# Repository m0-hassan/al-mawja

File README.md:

# AL-MAWJA

KiCad project for a mixed-signal I/Q analog front-end board (iCE40 FPGA, FT2232H USB, AD7380 ADC).

Work in progress — schematic is done, board layout is still underway. Not finished yet.

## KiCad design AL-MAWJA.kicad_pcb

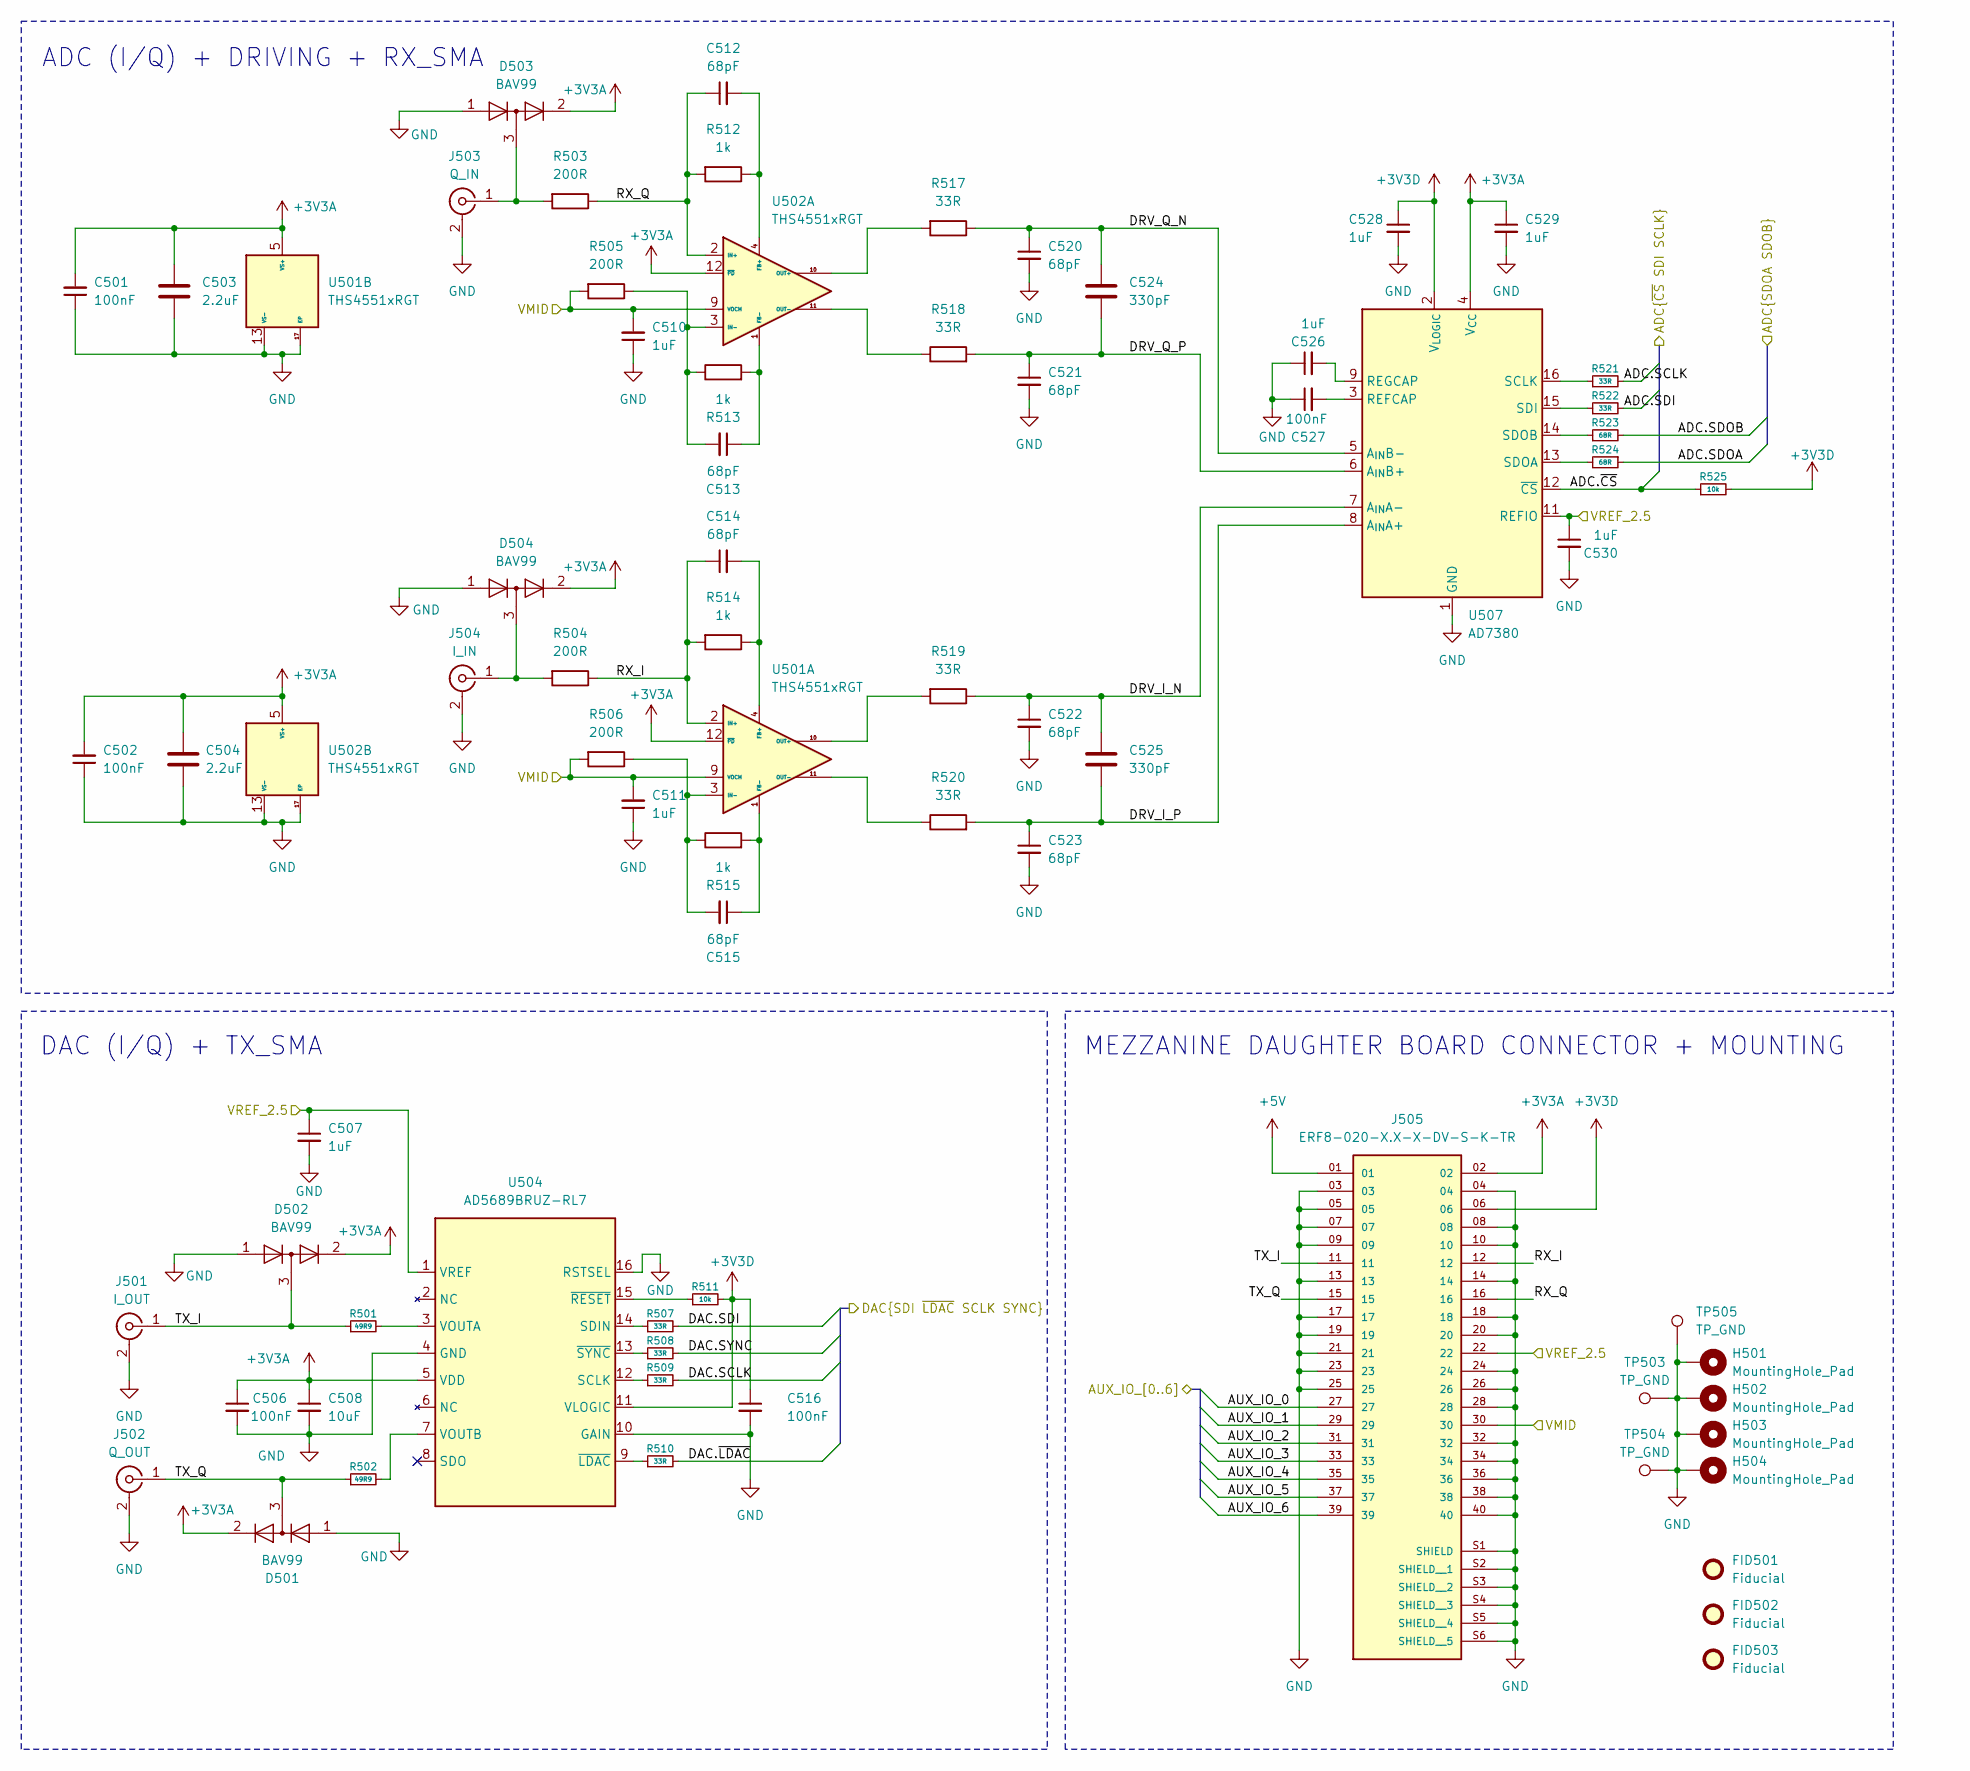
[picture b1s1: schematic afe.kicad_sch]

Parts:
C501, C502, C506, C516, C527: 100nF; C_0402_1005Metric
C503, C504: 2.2uF; C_0603_1608Metric
C507, C510, C511, C526, C528, C529, C530: 1uF; C_0603_1608Metric
C508: 10uF; C_0603_1608Metric
C512, C513, C514, C515, C520, C521, C522, C523: 68pF; C_0402_1005Metric
C524, C525: 330pF; C_0402_1005Metric
D501, D502, D503, D504: BAV99; SOT-23
FID501, FID502, FID503: Fiducial; Fiducial_1mm_Mask2mm
H501, H502, H503, H504: MountingHole_Pad; MountingHole_3.2mm_M3_Pad
J501: I_OUT; SMA_Amphenol_901-143_Horizontal
J502: Q_OUT; SMA_Amphenol_901-143_Horizontal
J503: Q_IN; SMA_Amphenol_901-143_Horizontal
J504: I_IN; SMA_Amphenol_901-143_Horizontal
J505: ERF8-020-X.X-X-DV-S-K-TR; Samtec_ERF8-020-DV; PARTREV N
R501, R502: 49R9; R_0402_1005Metric
R503, R504, R505, R506: 200R; R_0402_1005Metric
R507, R508, R509, R510, R517, R518, R519, R520, R521, R522: 33R; R_0402_1005Metric
R511, R525: 10k; R_0402_1005Metric
R512, R513, R514, R515: 1k; R_0402_1005Metric
R523, R524: 68R; R_0402_1005Metric
TP503, TP504, TP505: TP_GND; TestPoint_Pad_1.5x1.5mm
U501, U502: THS4551xRGT; THS4551_VQFN-16_3x3mm
U504: AD5689BRUZ-RL7; AD5689_TSSOP-16_4.4x5mm
U507: AD7380; AD7380_VQFN-16

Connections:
+3V3A: C501.2, C502.2, C503.1, C504.1, C506.1, C508.1, C529.1, D501.2 (A), D502.2 (A), D503.2 (A), D504.2 (A), J505.02, U501.5 (VS+), U501.6 (VS+), U501.7 (VS+), U501.8 (VS+), U501.12 (~PD), U502.5 (VS+), U502.6 (VS+), U502.7 (VS+), U502.8 (VS+), U502.12 (~PD), U504.5 (VDD), U507.4 (V_{CC}); also elsewhere on the board
+3V3D: C516.1, C528.1, J505.06, R511.2, R525.2, U504.11 (VLOGIC), U507.2 (V_{LOGIC}); also elsewhere on the board
+5V: J505.01; also elsewhere on the board
/Analog_Front_End_(AFE)/ADC.SCLK: R521.2; also elsewhere on the board
/Analog_Front_End_(AFE)/ADC.SDI: R522.2; also elsewhere on the board
/Analog_Front_End_(AFE)/ADC.SDOA: R524.1; also elsewhere on the board
/Analog_Front_End_(AFE)/ADC.SDOB: R523.2; also elsewhere on the board
/Analog_Front_End_(AFE)/ADC.~CS: R525.1, U507.12 (~CS); also elsewhere on the board
/Analog_Front_End_(AFE)/AUX_IO_0: J505.27; also elsewhere on the board
/Analog_Front_End_(AFE)/AUX_IO_1: J505.29; also elsewhere on the board
/Analog_Front_End_(AFE)/AUX_IO_2: J505.31; also elsewhere on the board
/Analog_Front_End_(AFE)/AUX_IO_3: J505.33; also elsewhere on the board
/Analog_Front_End_(AFE)/AUX_IO_4: J505.35; also elsewhere on the board
/Analog_Front_End_(AFE)/AUX_IO_5: J505.37; also elsewhere on the board
/Analog_Front_End_(AFE)/AUX_IO_6: J505.39; also elsewhere on the board
/Analog_Front_End_(AFE)/DAC.SCLK: R509.2; also elsewhere on the board
/Analog_Front_End_(AFE)/DAC.SDI: R507.2; also elsewhere on the board
/Analog_Front_End_(AFE)/DAC.SYNC: R508.2; also elsewhere on the board
/Analog_Front_End_(AFE)/DAC.~LDAC: R510.2; also elsewhere on the board
/Analog_Front_End_(AFE)/DRV_I_N: C522.1, C525.1, R519.1, U507.7 (A_{IN}A-)
/Analog_Front_End_(AFE)/DRV_I_P: C523.1, C525.2, R520.2, U507.8 (A_{IN}A+)
/Analog_Front_End_(AFE)/DRV_Q_N: C520.1, C524.1, R517.1, U507.5 (A_{IN}B-)
/Analog_Front_End_(AFE)/DRV_Q_P: C521.1, C524.2, R518.2, U507.6 (A_{IN}B+)
/Analog_Front_End_(AFE)/RX_I: C514.1, J505.12, R504.1, R514.2, U501.2 (IN+)
/Analog_Front_End_(AFE)/RX_Q: C512.1, J505.16, R503.1, R512.2, U502.2 (IN+)
/Analog_Front_End_(AFE)/TX_I: D502.3 (K), J501.1 (In), J505.11, R501.1
/Analog_Front_End_(AFE)/TX_Q: D501.3 (K), J502.1 (In), J505.15, R502.1
/Analog_Front_End_(AFE)/VMID: C510.2, C511.2, J505.30, R505.2, R506.2, U501.9 (VOCM), U502.9 (VOCM); also elsewhere on the board
/Analog_Front_End_(AFE)/VREF_2.5: C507.1, C530.1, J505.22, U504.1 (VREF), U507.11 (REFIO); also elsewhere on the board
GND: C501.1, C502.1, C503.2, C504.2, C506.2, C507.2, C508.2, C510.1, C511.1, C516.2, C520.2, C521.2, C522.2, C523.2, C526.1, C527.1, C528.2, C529.2, C530.2, D501.1 (K), D502.1 (K), D503.1 (K), D504.1 (K), H501.1 (1_1), H502.1 (1_1), H503.1 (1_1), H504.1 (1_1), J501.2 (Ext), J502.2 (Ext), J503.2 (Ext), J504.2 (Ext), J505.03, J505.04, J505.05, J505.07, J505.08, J505.09, J505.10, J505.13, J505.14, J505.17, J505.18, J505.19, J505.20, J505.21, J505.23, J505.24, J505.25, J505.26, J505.28, J505.32, J505.34, J505.36, J505.38, J505.40, J505.S1 (SHIELD), J505.S2 (SHIELD__1), J505.S3 (SHIELD__2), J505.S4 (SHIELD__3), J505.S5 (SHIELD__4), J505.S6 (SHIELD__5), TP503.1 (1_1), TP504.1 (1_1), TP505.1 (1_1), U501.13 (VS-), U501.14 (VS-), U501.15 (VS-), U501.16 (VS-), U501.17 (EP), U502.13 (VS-), U502.14 (VS-), U502.15 (VS-), U502.16 (VS-), U502.17 (EP), U504.4 (GND), U504.10 (GAIN), U504.16 (RSTSEL), U507.1 (GND), U507.10 (GND); also elsewhere on the board
unnamed: D503.3 (K), J503.1 (In), R503.2
unnamed: D504.3 (K), J504.1 (In), R504.2
unnamed: C514.2, R514.1, U501.4 (FB+)
unnamed: C515.1, R515.2, U501.1 (FB-)
unnamed: C515.2, R506.1, R515.1, U501.3 (IN-)
unnamed: R519.2, U501.10 (OUT+)
unnamed: R520.1, U501.11 (OUT-)
unnamed: C512.2, R512.1, U502.4 (FB+)
unnamed: C513.1, R513.2, U502.1 (FB-)
unnamed: C513.2, R505.1, R513.1, U502.3 (IN-)
unnamed: R517.2, U502.10 (OUT+)
unnamed: R518.1, U502.11 (OUT-)
unnamed: R509.1, U504.12 (SCLK)
unnamed: R507.1, U504.14 (SDIN)
unnamed: R501.2, U504.3 (VOUTA)
unnamed: R502.2, U504.7 (VOUTB)
unnamed: R510.1, U504.9 (~LDAC)
unnamed: R511.1, U504.15 (~RESET)
unnamed: R508.1, U504.13 (~SYNC)
unnamed: C527.2, U507.3 (REFCAP)
unnamed: C526.2, U507.9 (REGCAP)
unnamed: R521.1, U507.16 (SCLK)
unnamed: R522.1, U507.15 (SDI)
unnamed: R524.2, U507.13 (SDOA)
unnamed: R523.1, U507.14 (SDOB)

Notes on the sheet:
DAC (I/Q) + TX_SMA
MEZZANINE DAUGHTER BOARD CONNECTOR + MOUNTING
ADC (I/Q) + DRIVING + RX_SMA

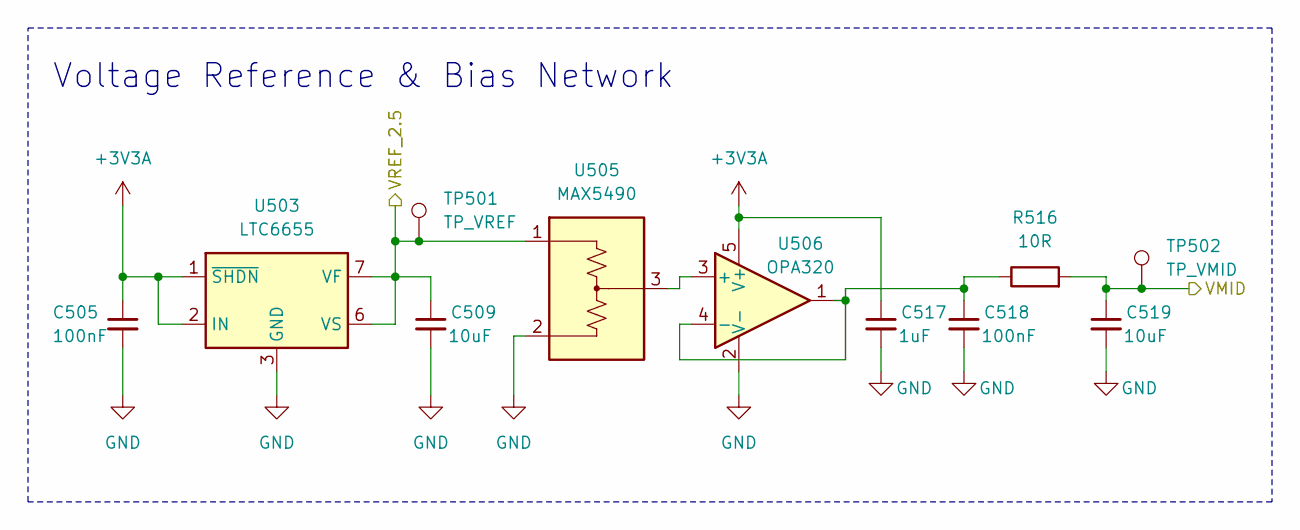
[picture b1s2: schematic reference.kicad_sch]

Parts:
C505, C518: 100nF; C_0402_1005Metric
C509, C519: 10uF; C_0603_1608Metric
C517: 1uF; C_0603_1608Metric
R516: 10R; R_0402_1005Metric
TP501: TP_VREF; TestPoint_Pad_D1.5mm
TP502: TP_VMID; TestPoint_Pad_D1.5mm
U503: LTC6655; LTC6655_LCC-8_5x5mm
U505: MAX5490; MAX5490_SOT-23
U506: OPA320; OPA320_SOT-23-6

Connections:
+3V3A: C505.1, C517.1, U503.1 (~SHDN), U503.2 (IN), U506.5 (V+); also elsewhere on the board
/Analog_Front_End_(AFE)/VMID: C519.1, R516.2, TP502.1 (1_1); also elsewhere on the board
/Analog_Front_End_(AFE)/VREF_2.5: C509.1, TP501.1 (1_1), U503.6 (VS), U503.7 (VF), U505.1; also elsewhere on the board
GND: C505.2, C509.2, C517.2, C518.2, C519.2, U503.3 (GND), U503.4 (GND), U503.5 (GND), U503.8 (GND), U505.2, U506.2 (V-); also elsewhere on the board
unnamed: U505.3, U506.3 (+)
unnamed: C518.1, R516.1, U506.1, U506.4 (-)

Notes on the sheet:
Voltage Reference & Bias Network

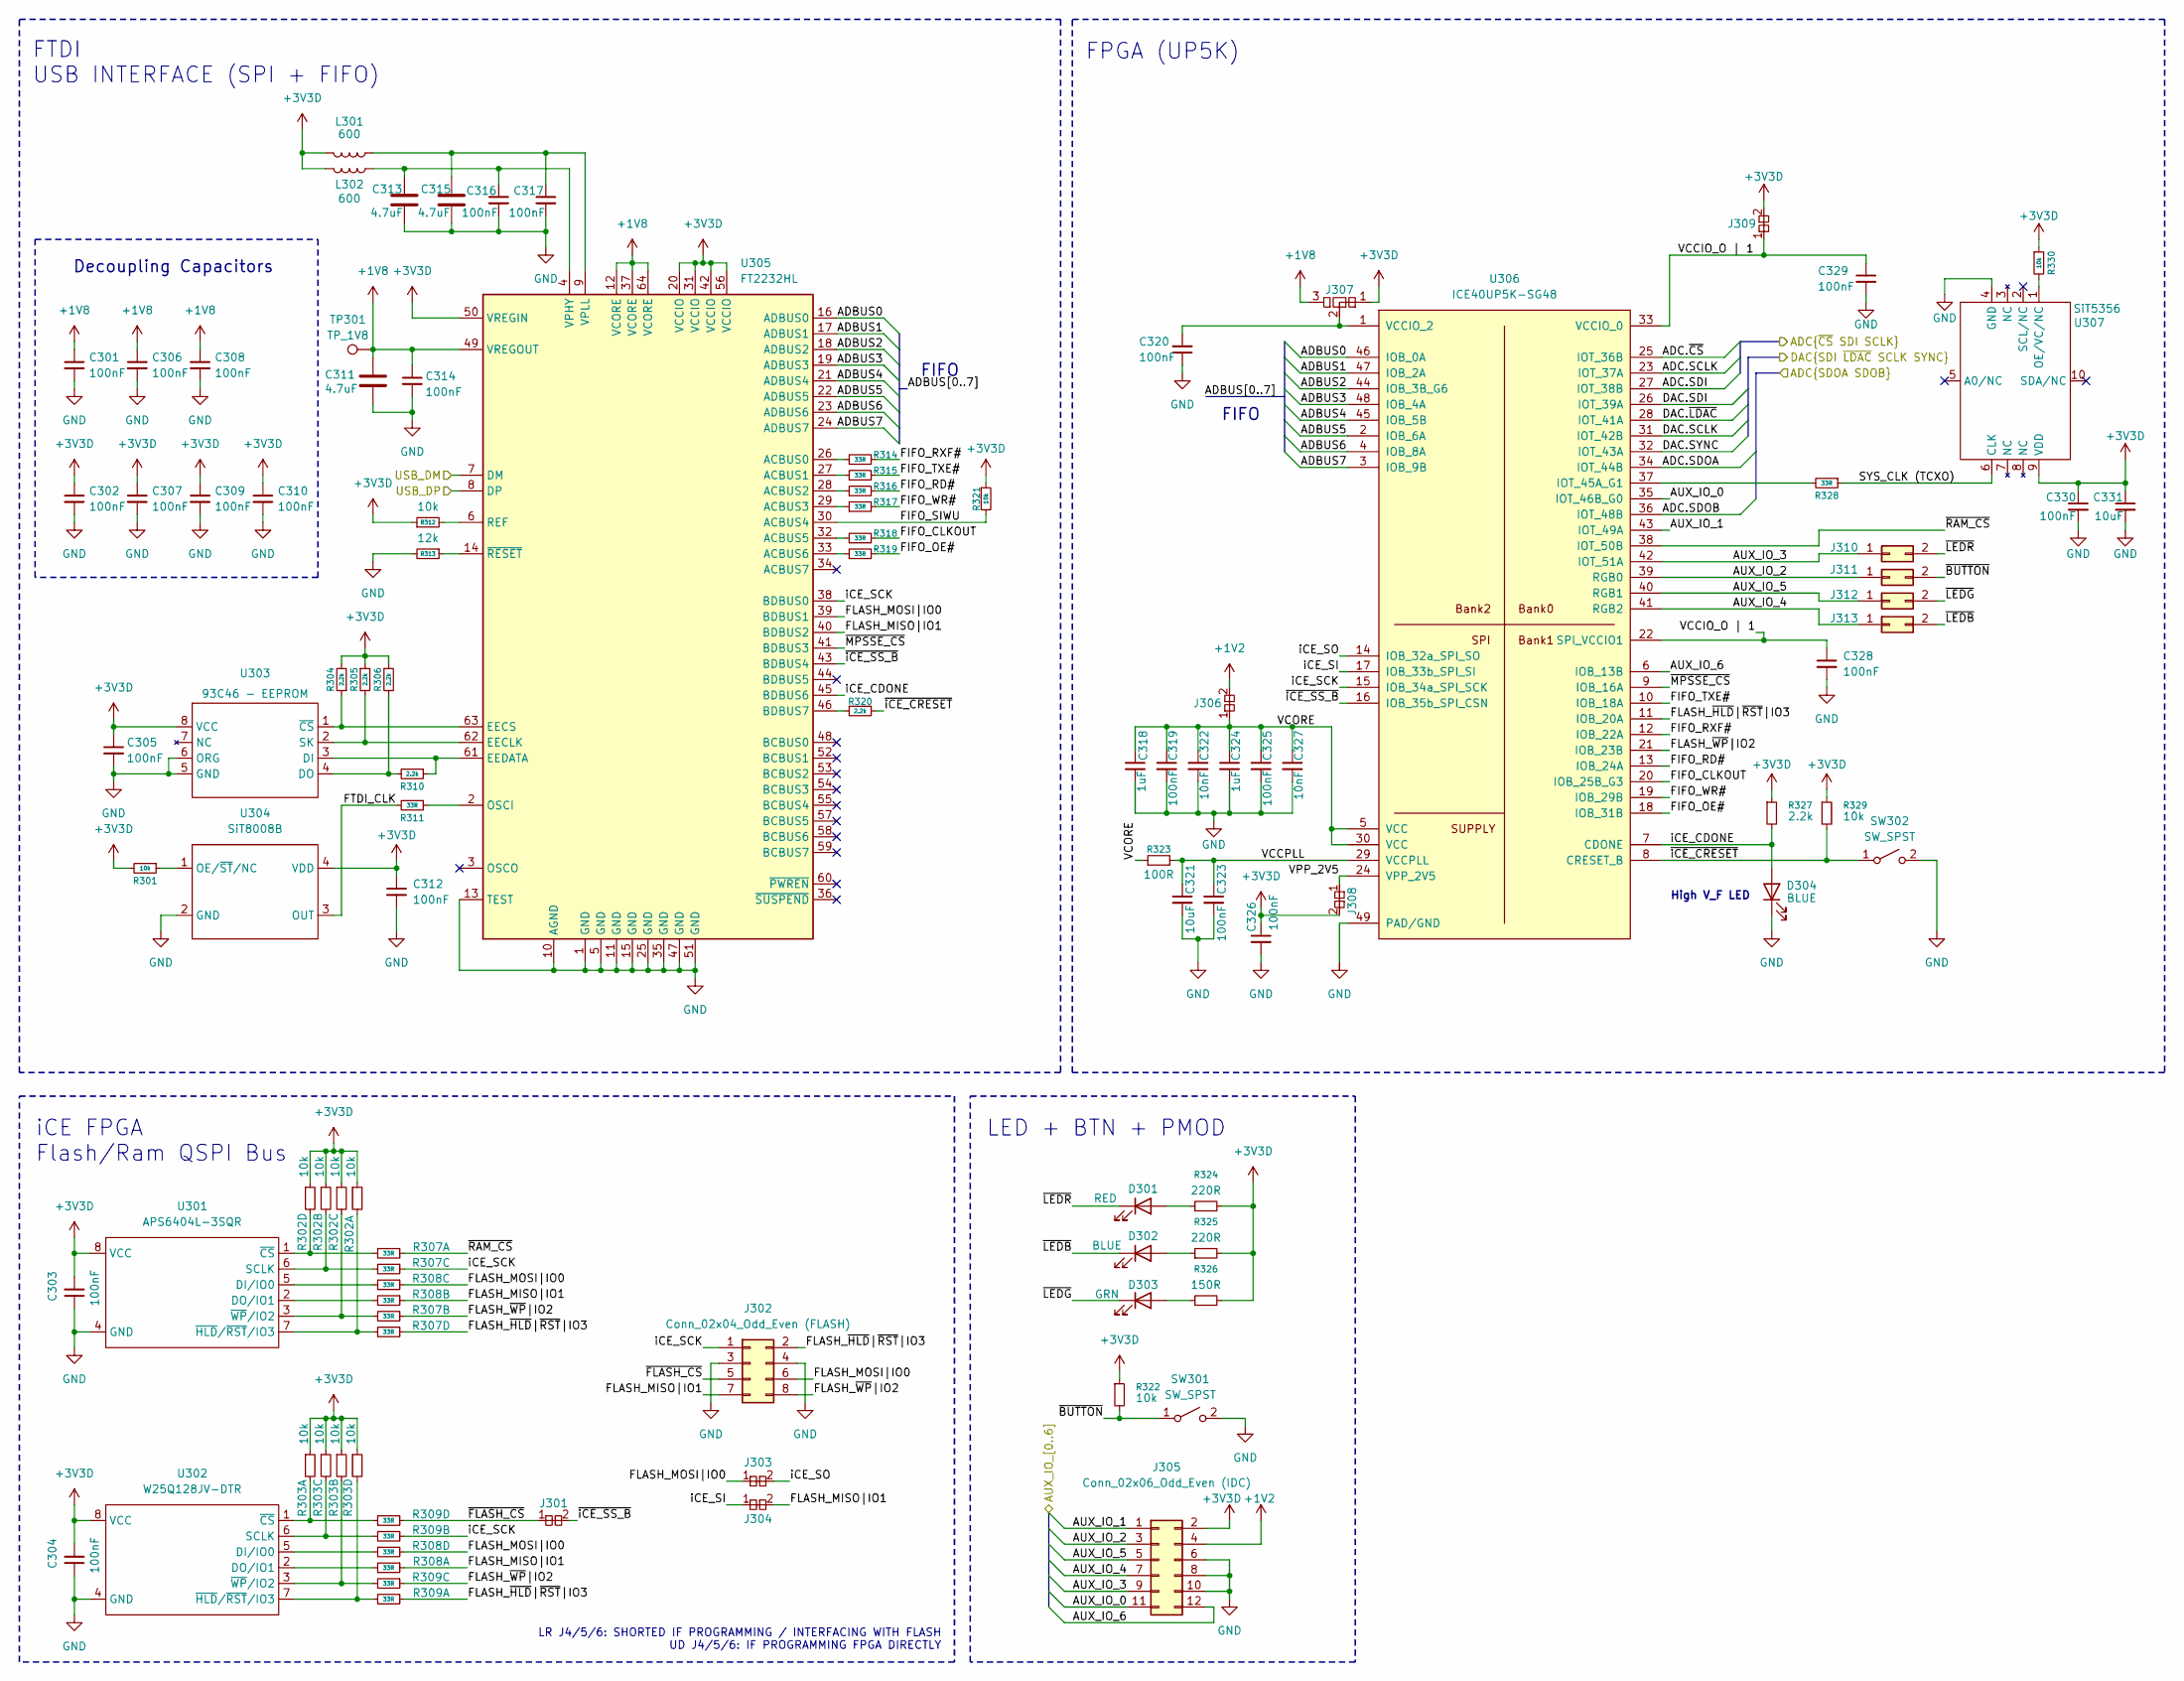
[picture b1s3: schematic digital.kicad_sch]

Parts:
C301, C302, C303, C304, C305, C306, C307, C308, C309, C310, C312, C314, C316, C317, C319, C320, C323, C325, C326, C328, C329, C330: 100nF; C_0402_1005Metric
C311, C313, C315: 4.7uF; C_0603_1608Metric
C318, C324: 1uF; C_0603_1608Metric
C321, C331: 10uF; C_0603_1608Metric
C322, C327: 10nF; C_0402_1005Metric
D301: RED; LED_0603_1608Metric
D302, D304: BLUE; LED_0603_1608Metric
D303: GRN; LED_0603_1608Metric
J301, J303, J304, J306, J308, J309: pkl_jumper_nc; SolderJumper-2_P1.3mm_Bridged_RoundedPad1.0x1.5mm
J302: Conn_02x04_Odd_Even (FLASH); IDC-Header_2x04_P2.54mm_Horizontal
J305: Conn_02x06_Odd_Even (IDC); IDC-Header_2x06_P2.54mm_Horizontal
J307: pkl_double_jumper_ncno; SolderJumper-3_P1.3mm_Bridged12_RoundedPad1.0x1.5mm
J310, J311, J312, J313: Conn_02x01; PinHeader_2x01_P2.54mm_Horizontal
L301, L302: 600; L_0603_1608Metric
R301, R312, R321, R322, R329, R330: 10k; R_0402_1005Metric
R302, R303: 10k; R_Array_Convex_4x0402
R304, R305, R306, R310, R320, R327: 2.2k; R_0402_1005Metric
R307, R308, R309: 33R; R_Array_Convex_4x0402
R311, R314, R315, R316, R317, R318, R319, R328: 33R; R_0402_1005Metric
R313: 12k; R_0402_1005Metric
R323: 100R; R_0402_1005Metric
R324, R325: 220R; R_0402_1005Metric
R326: 150R; R_0402_1005Metric
SW301, SW302: SW_SPST; SW_PUSH_6mm_H4.3mm
TP301: TP_1V8; TestPoint_Pad_D1.5mm
U301: APS6404L-3SQR; SOIC-8_3.9x4.9mm_P1.27mm
U302: W25Q128JV-DTR; W25Q128JV_SOIC-8_5.3x5.3mm
U303: 93C46 - EEPROM; SOIC-8_3.9x4.9mm_P1.27mm
U304: SiT8008B; SiT8008B_PQFN-4_3.2x2.5mm
U305: FT2232HL; FT2232HL_LQFP-64_10x10mm
U306: ICE40UP5K-SG48; iCE40UP5K_QFN-48_7x7mm
U307: SiT5356; SiT5356_PQFN-4_3.2x2.5mm

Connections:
+1V2: J305.4, J306.2; also elsewhere on the board
+1V8: C301.1, C306.1, C308.1, C311.1, C314.1, J307.3, TP301.1 (1_1), U305.12 (VCORE), U305.37 (VCORE), U305.49 (VREGOUT), U305.64 (VCORE)
+3V3D: C302.1, C303.2, C304.2, C305.1, C307.1, C309.1, C310.1, C312.1, C326.1, C330.1, C331.1, J305.2, J307.1, J308.2, J309.2, L301.2, L302.2, R301.2, R302.1, R302.3, R302.5, R302.7, R303.1, R303.3, R303.5, R303.7, R304.2, R305.1, R306.1, R312.1, R321.1, R322.1, R324.2, R325.2, R326.2, R327.1, R329.1, R330.1, U301.8 (VCC), U302.8 (VCC), U303.8 (VCC), U304.4 (VDD), U305.20 (VCCIO), U305.31 (VCCIO), U305.42 (VCCIO), U305.50 (VREGIN), U305.56 (VCCIO), U307.9 (VDD); also elsewhere on the board
/Analog_Front_End_(AFE)/ADC.SCLK: U306.23 (IOT_37A); also elsewhere on the board
/Analog_Front_End_(AFE)/ADC.SDI: U306.27 (IOT_38B); also elsewhere on the board
/Analog_Front_End_(AFE)/ADC.SDOA: U306.34 (IOT_44B); also elsewhere on the board
/Analog_Front_End_(AFE)/ADC.SDOB: U306.36 (IOT_48B); also elsewhere on the board
/Analog_Front_End_(AFE)/ADC.~CS: U306.25 (IOT_36B); also elsewhere on the board
/Analog_Front_End_(AFE)/AUX_IO_0: J305.11, U306.35 (IOT_46B_G0); also elsewhere on the board
/Analog_Front_End_(AFE)/AUX_IO_1: J305.1, U306.43 (IOT_49A); also elsewhere on the board
/Analog_Front_End_(AFE)/AUX_IO_2: J305.3, J311.1, U306.39 (RGB0); also elsewhere on the board
/Analog_Front_End_(AFE)/AUX_IO_3: J305.9, J310.1, U306.42 (IOT_51A); also elsewhere on the board
/Analog_Front_End_(AFE)/AUX_IO_4: J305.7, J313.1, U306.41 (RGB2); also elsewhere on the board
/Analog_Front_End_(AFE)/AUX_IO_5: J305.5, J312.1, U306.40 (RGB1); also elsewhere on the board
/Analog_Front_End_(AFE)/AUX_IO_6: J305.12, U306.6 (IOB_13B); also elsewhere on the board
/Analog_Front_End_(AFE)/DAC.SCLK: U306.31 (IOT_42B); also elsewhere on the board
/Analog_Front_End_(AFE)/DAC.SDI: U306.26 (IOT_39A); also elsewhere on the board
/Analog_Front_End_(AFE)/DAC.SYNC: U306.32 (IOT_43A); also elsewhere on the board
/Analog_Front_End_(AFE)/DAC.~LDAC: U306.28 (IOT_41A); also elsewhere on the board
/Digital_Core/ADBUS0: U305.16 (ADBUS0), U306.46 (IOB_0A)
/Digital_Core/ADBUS1: U305.17 (ADBUS1), U306.47 (IOB_2A)
/Digital_Core/ADBUS2: U305.18 (ADBUS2), U306.44 (IOB_3B_G6)
/Digital_Core/ADBUS3: U305.19 (ADBUS3), U306.48 (IOB_4A)
/Digital_Core/ADBUS4: U305.21 (ADBUS4), U306.45 (IOB_5B)
/Digital_Core/ADBUS5: U305.22 (ADBUS5), U306.2 (IOB_6A)
/Digital_Core/ADBUS6: U305.23 (ADBUS6), U306.4 (IOB_8A)
/Digital_Core/ADBUS7: U305.24 (ADBUS7), U306.3 (IOB_9B)
/Digital_Core/FIFO_CLKOUT: R318.2, U306.20 (IOB_25B_G3)
/Digital_Core/FIFO_OE#: R319.2, U306.18 (IOB_31B)
/Digital_Core/FIFO_RD#: R316.2, U306.13 (IOB_24A)
/Digital_Core/FIFO_RXF#: R314.2, U306.12 (IOB_22A)
/Digital_Core/FIFO_SIWU: R321.2, U305.30 (ACBUS4)
/Digital_Core/FIFO_TXE#: R315.2, U306.10 (IOB_18A)
/Digital_Core/FIFO_WR#: R317.2, U306.19 (IOB_29B)
/Digital_Core/FLASH_MISO|IO1: J302.7, J304.2, R308.1, R308.3, U305.40 (BDBUS2)
/Digital_Core/FLASH_MOSI|IO0: J302.6, J303.1, R308.5, R308.7, U305.39 (BDBUS1)
/Digital_Core/FLASH_~HLD|~RST|IO3: J302.2, R307.7, R309.1, U306.11 (IOB_20A)
/Digital_Core/FLASH_~WP|IO2: J302.8, R307.3, R309.5, U306.21 (IOB_23B)
/Digital_Core/FTDI_CLK: R311.2, U304.3 (OUT)
/Digital_Core/SYS_CLK (TCXO): R328.1, U307.6 (CLK)
/Digital_Core/USB_DM: U305.7 (DM); also elsewhere on the board
/Digital_Core/USB_DP: U305.8 (DP); also elsewhere on the board
/Digital_Core/VCCIO_O | 1: C328.1, C329.1, J309.1, U306.22 (SPI_VCCIO1), U306.33 (VCCIO_0)
/Digital_Core/VCCPLL: C321.1, C323.1, R323.2, U306.29 (VCCPLL)
/Digital_Core/VCORE: C318.1, C319.1, C322.1, C324.1, C325.1, C327.1, J306.1, R323.1, U306.5 (VCC), U306.30 (VCC)
/Digital_Core/VPP_2V5: J308.1, U306.24 (VPP_2V5)
/Digital_Core/iCE_CDONE: D304.2 (A), R327.2, U305.45 (BDBUS6), U306.7 (CDONE)
/Digital_Core/iCE_SCK: J302.1, R307.5, R309.3, U305.38 (BDBUS0), U306.15 (IOB_34a_SPI_SCK)
/Digital_Core/iCE_SI: J304.1, U306.17 (IOB_33b_SPI_SI)
/Digital_Core/iCE_SO: J303.2, U306.14 (IOB_32a_SPI_SO)
/Digital_Core/~BUTTON: J311.2, R322.2, SW301.1 (A)
/Digital_Core/~FLASH_CS: J301.1, J302.5, R309.7
/Digital_Core/~LEDB: D302.1 (K), J313.2
/Digital_Core/~LEDG: D303.1 (K), J312.2
/Digital_Core/~LEDR: D301.1 (K), J310.2
/Digital_Core/~MPSSE_CS: U305.41 (BDBUS3), U306.9 (IOB_16A)
/Digital_Core/~RAM_CS: R307.1, U306.38 (IOT_50B)
/Digital_Core/~iCE_CRESET: R320.1, R329.2, SW302.1 (A), U306.8 (CRESET_B)
/Digital_Core/~iCE_SS_B: J301.2, U305.43 (BDBUS4), U306.16 (IOB_35b_SPI_CSN)
GND: C301.2, C302.2, C303.1, C304.1, C305.2, C306.2, C307.2, C308.2, C309.2, C310.2, C311.2, C312.2, C313.2, C314.2, C315.2, C316.2, C317.2, C318.2, C319.2, C320.1, C321.2, C322.2, C323.2, C324.2, C325.2, C326.2, C327.2, C328.2, C329.2, C330.2, C331.2, D304.1 (K), J302.3, J302.4, J305.6, J305.8, J305.10, R313.2, SW301.2 (B), SW302.2 (B), U301.4 (GND), U302.4 (GND), U303.5 (GND), U303.6 (ORG), U304.2 (GND), U305.1 (GND), U305.5 (GND), U305.10 (AGND), U305.11 (GND), U305.13 (TEST), U305.15 (GND), U305.25 (GND), U305.35 (GND), U305.47 (GND), U305.51 (GND), U306.49 (PAD/GND), U307.4 (GND); also elsewhere on the board
unnamed: D301.2 (A), R324.1
unnamed: D302.2 (A), R325.1
unnamed: D303.2 (A), R326.1
unnamed: R308.6, U301.5 (DI/IO0)
unnamed: R308.4, U301.2 (DO/IO1)
unnamed: R302.4, R307.6, U301.6 (SCLK)
unnamed: R302.8, R307.2, U301.1 (~CS)
unnamed: R302.2, R307.8, U301.7 (~HLD/~RST/IO3)
unnamed: R302.6, R307.4, U301.3 (~WP/IO2)
unnamed: R308.8, U302.5 (DI/IO0)
unnamed: R308.2, U302.2 (DO/IO1)
unnamed: R303.6, R309.4, U302.6 (SCLK)
unnamed: R303.2, R309.8, U302.1 (~CS)
unnamed: R303.8, R309.2, U302.7 (~HLD/~RST/IO3)
unnamed: R303.4, R309.6, U302.3 (~WP/IO2)
unnamed: R310.1, U303.3 (DI), U305.61 (EEDATA)
unnamed: R306.2, R310.2, U303.4 (DO)
unnamed: R305.2, U303.2 (SK), U305.62 (EECLK)
unnamed: R304.1, U303.1 (~CS), U305.63 (EECS)
unnamed: R301.1, U304.1 (OE/~ST/NC)
unnamed: R314.1, U305.26 (ACBUS0)
unnamed: R315.1, U305.27 (ACBUS1)
unnamed: R316.1, U305.28 (ACBUS2)
unnamed: R317.1, U305.29 (ACBUS3)
unnamed: R318.1, U305.32 (ACBUS5)
unnamed: R319.1, U305.33 (ACBUS6)
unnamed: R320.2, U305.46 (BDBUS7)
unnamed: R311.1, U305.2 (OSCI)
unnamed: R312.2, U305.6 (REF)
unnamed: C313.1, C316.1, L302.1, U305.4 (VPHY)
unnamed: C315.1, C317.1, L301.1, U305.9 (VPLL)
unnamed: R313.1, U305.14 (~RESET)
unnamed: R328.2, U306.37 (IOT_45A_G1)
unnamed: C320.2, J307.2, U306.1 (VCCIO_2)
unnamed: R330.2, U307.1 (OE/VC/NC)

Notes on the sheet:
FIFO
High V_F LED
LR J4/5/6: SHORTED IF PROGRAMMING / INTERFACING WITH FLASH UD J4/5/6: IF PROGRAMMING FPGA DIRECTLY
FPGA (UP5K)
Decoupling Capacitors
iCE FPGA Flash/Ram QSPI Bus
LED + BTN + PMOD
FTDI USB INTERFACE (SPI + FIFO)

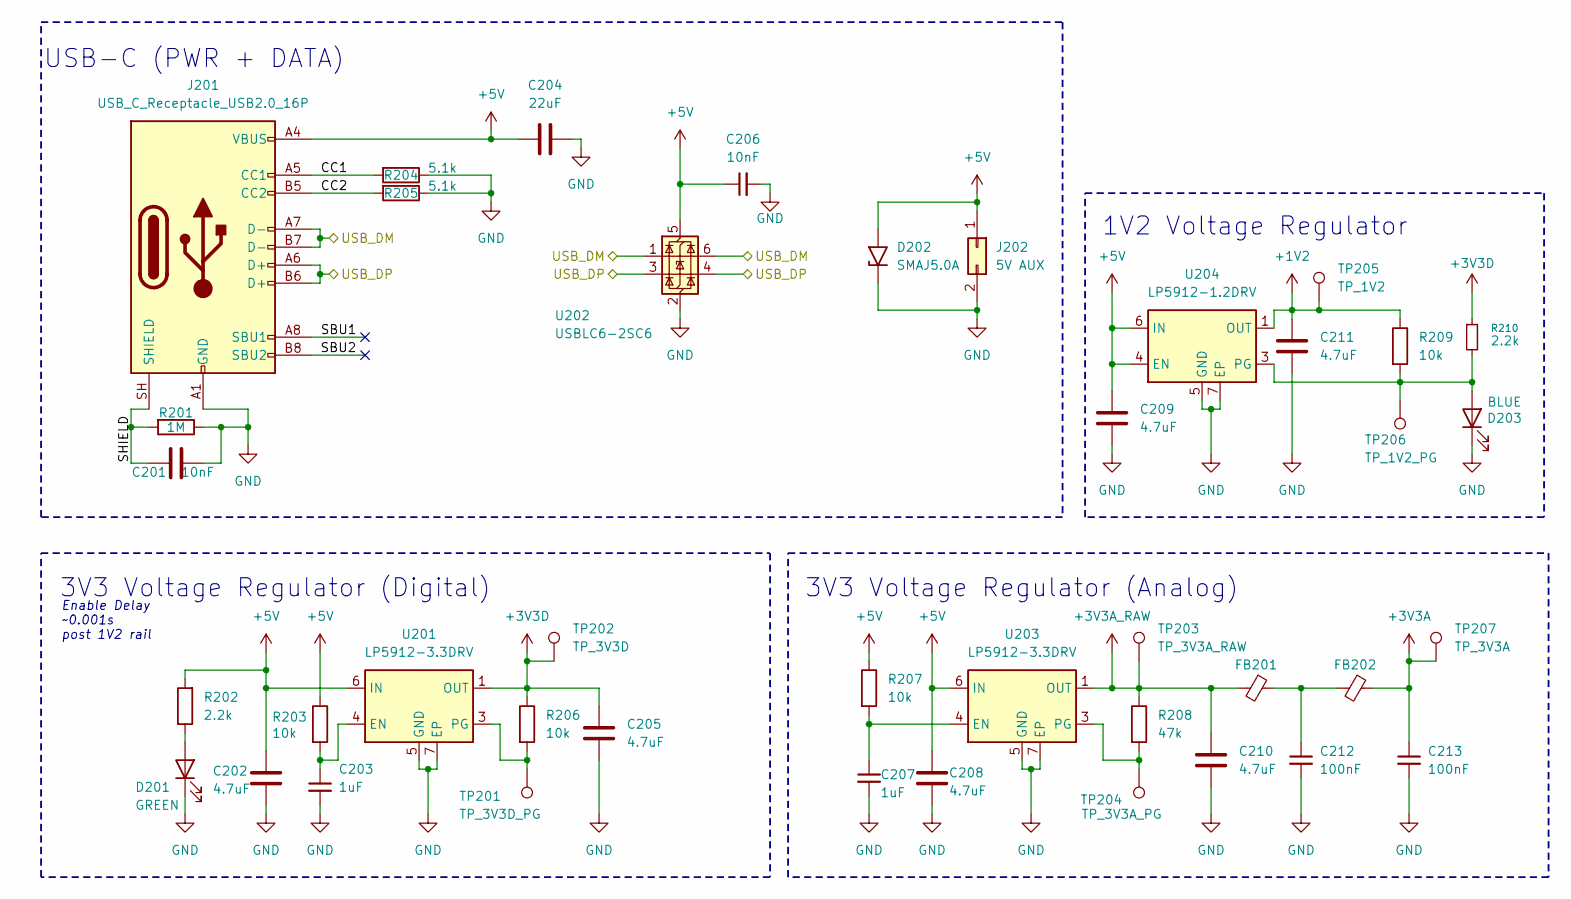
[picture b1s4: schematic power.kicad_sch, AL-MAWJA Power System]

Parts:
C201, C206: 10nF; C_0402_1005Metric
C202, C205, C208, C209, C210, C211: 4.7uF; C_0603_1608Metric
C203, C207: 1uF; C_0603_1608Metric
C204: 22uF; C_0805_2012Metric
C212, C213: 100nF; C_0402_1005Metric
D201: GREEN; LED_0603_1608Metric
D202: SMAJ5.0A; D_SMA
D203: BLUE; LED_0603_1608Metric
FB201, FB202: 600R @ 100MHz; L_0603_1608Metric
J201: USB_C_Receptacle_USB2.0_16P; USB-C_Amphenol_12401610E4-2A
J202: 5V AUX; PinHeader_1x02_P1.00mm_Vertical
R201: 1M; R_0402_1005Metric
R202, R210: 2.2k; R_0402_1005Metric
R203, R206, R207, R209: 10k; R_0402_1005Metric
R204, R205: 5.1k; R_0402_1005Metric
R208: 47k; R_0402_1005Metric
TP201: TP_3V3D_PG; TestPoint_Pad_D1.5mm
TP202: TP_3V3D; TestPoint_Pad_D1.5mm
TP203: TP_3V3A_RAW; TestPoint_Pad_D1.5mm
TP204: TP_3V3A_PG; TestPoint_Pad_D1.5mm
TP205: TP_1V2; TestPoint_Pad_D1.5mm
TP206: TP_1V2_PG; TestPoint_Pad_D1.5mm
TP207: TP_3V3A; TestPoint_Pad_D1.5mm
U201, U203: LP5912-3.3DRV; LP5912_WSON-6_2x2mm
U202: USBLC6-2SC6; SOT-23-6
U204: LP5912-1.2DRV; LP5912_WSON-6_2x2mm

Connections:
+1V2: C211.1, R209.1, TP205.1 (1_1), U204.1 (OUT); also elsewhere on the board
+3V3A: C213.1, FB202.1, TP207.1 (1_1); also elsewhere on the board
+3V3A_RAW: C210.2, FB201.2, R208.1, TP203.1 (1_1), U203.1 (OUT)
+3V3D: C205.1, R206.1, R210.1, TP202.1 (1_1), U201.1 (OUT); also elsewhere on the board
+5V: C202.1, C204.1, C206.1, C208.1, C209.1, D202.2 (A2), J201.A4 (VBUS), J201.A9 (VBUS), J201.B4 (VBUS), J201.B9 (VBUS), J202.1, R202.2, R203.1, R207.1, U201.6 (IN), U202.5 (VBUS), U203.6 (IN), U204.4 (EN), U204.6 (IN); also elsewhere on the board
/Digital_Core/USB_DM: J201.A7 (D-), J201.B7 (D-), U202.1 (I/O1), U202.6 (I/O1); also elsewhere on the board
/Digital_Core/USB_DP: J201.A6 (D+), J201.B6 (D+), U202.3 (I/O2), U202.4 (I/O2); also elsewhere on the board
/Power_System/CC1: J201.A5 (CC1), R204.2
/Power_System/CC2: J201.B5 (CC2), R205.2
/Power_System/SBU1: J201.A8 (SBU1)
/Power_System/SBU2: J201.B8 (SBU2)
/Power_System/SHIELD: C201.1, J201.SH (SHIELD), R201.2
GND: C201.2, C202.2, C203.2, C204.2, C205.2, C206.2, C207.2, C208.2, C209.2, C210.1, C211.2, C212.2, C213.2, D201.1 (K), D202.1 (A1), D203.1 (K), J201.A1 (GND), J201.A12 (GND), J201.B1 (GND), J201.B12 (GND), J202.2, R201.1, R204.1, R205.1, U201.5 (GND), U201.7 (EP), U202.2 (GND), U203.5 (GND), U203.7 (EP), U204.5 (GND), U204.7 (EP); also elsewhere on the board
unnamed: C212.1, FB201.1, FB202.2
unnamed: D201.2 (A), R202.1
unnamed: D203.2 (A), R209.2, R210.2, TP206.1 (1_1), U204.3 (PG)
unnamed: C203.1, R203.2, U201.4 (EN)
unnamed: R206.2, TP201.1 (1_1), U201.3 (PG)
unnamed: C207.1, R207.2, U203.4 (EN)
unnamed: R208.2, TP204.1 (1_1), U203.3 (PG)

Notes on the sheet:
3V3 Voltage Regulator (Analog)
1V2 Voltage Regulator
Enable Delay ~0.001s post 1V2 rail
USB-C (PWR + DATA)
3V3 Voltage Regulator (Digital)

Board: 4 copper layers, 214 parts (11 on the bottom side), 145 nets, no tracks yet.

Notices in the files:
Al-Mawja Datasheets/IceBreakerReference/icebreaker.kicad_pcb:
(C) 2019 Piotr Esden-Tempski
(C) 2019 1BitSquared
License: CC-BY-SA 4.0
(C) 2019
1B2 (C) 2019
CC-BY-SA 4.0
